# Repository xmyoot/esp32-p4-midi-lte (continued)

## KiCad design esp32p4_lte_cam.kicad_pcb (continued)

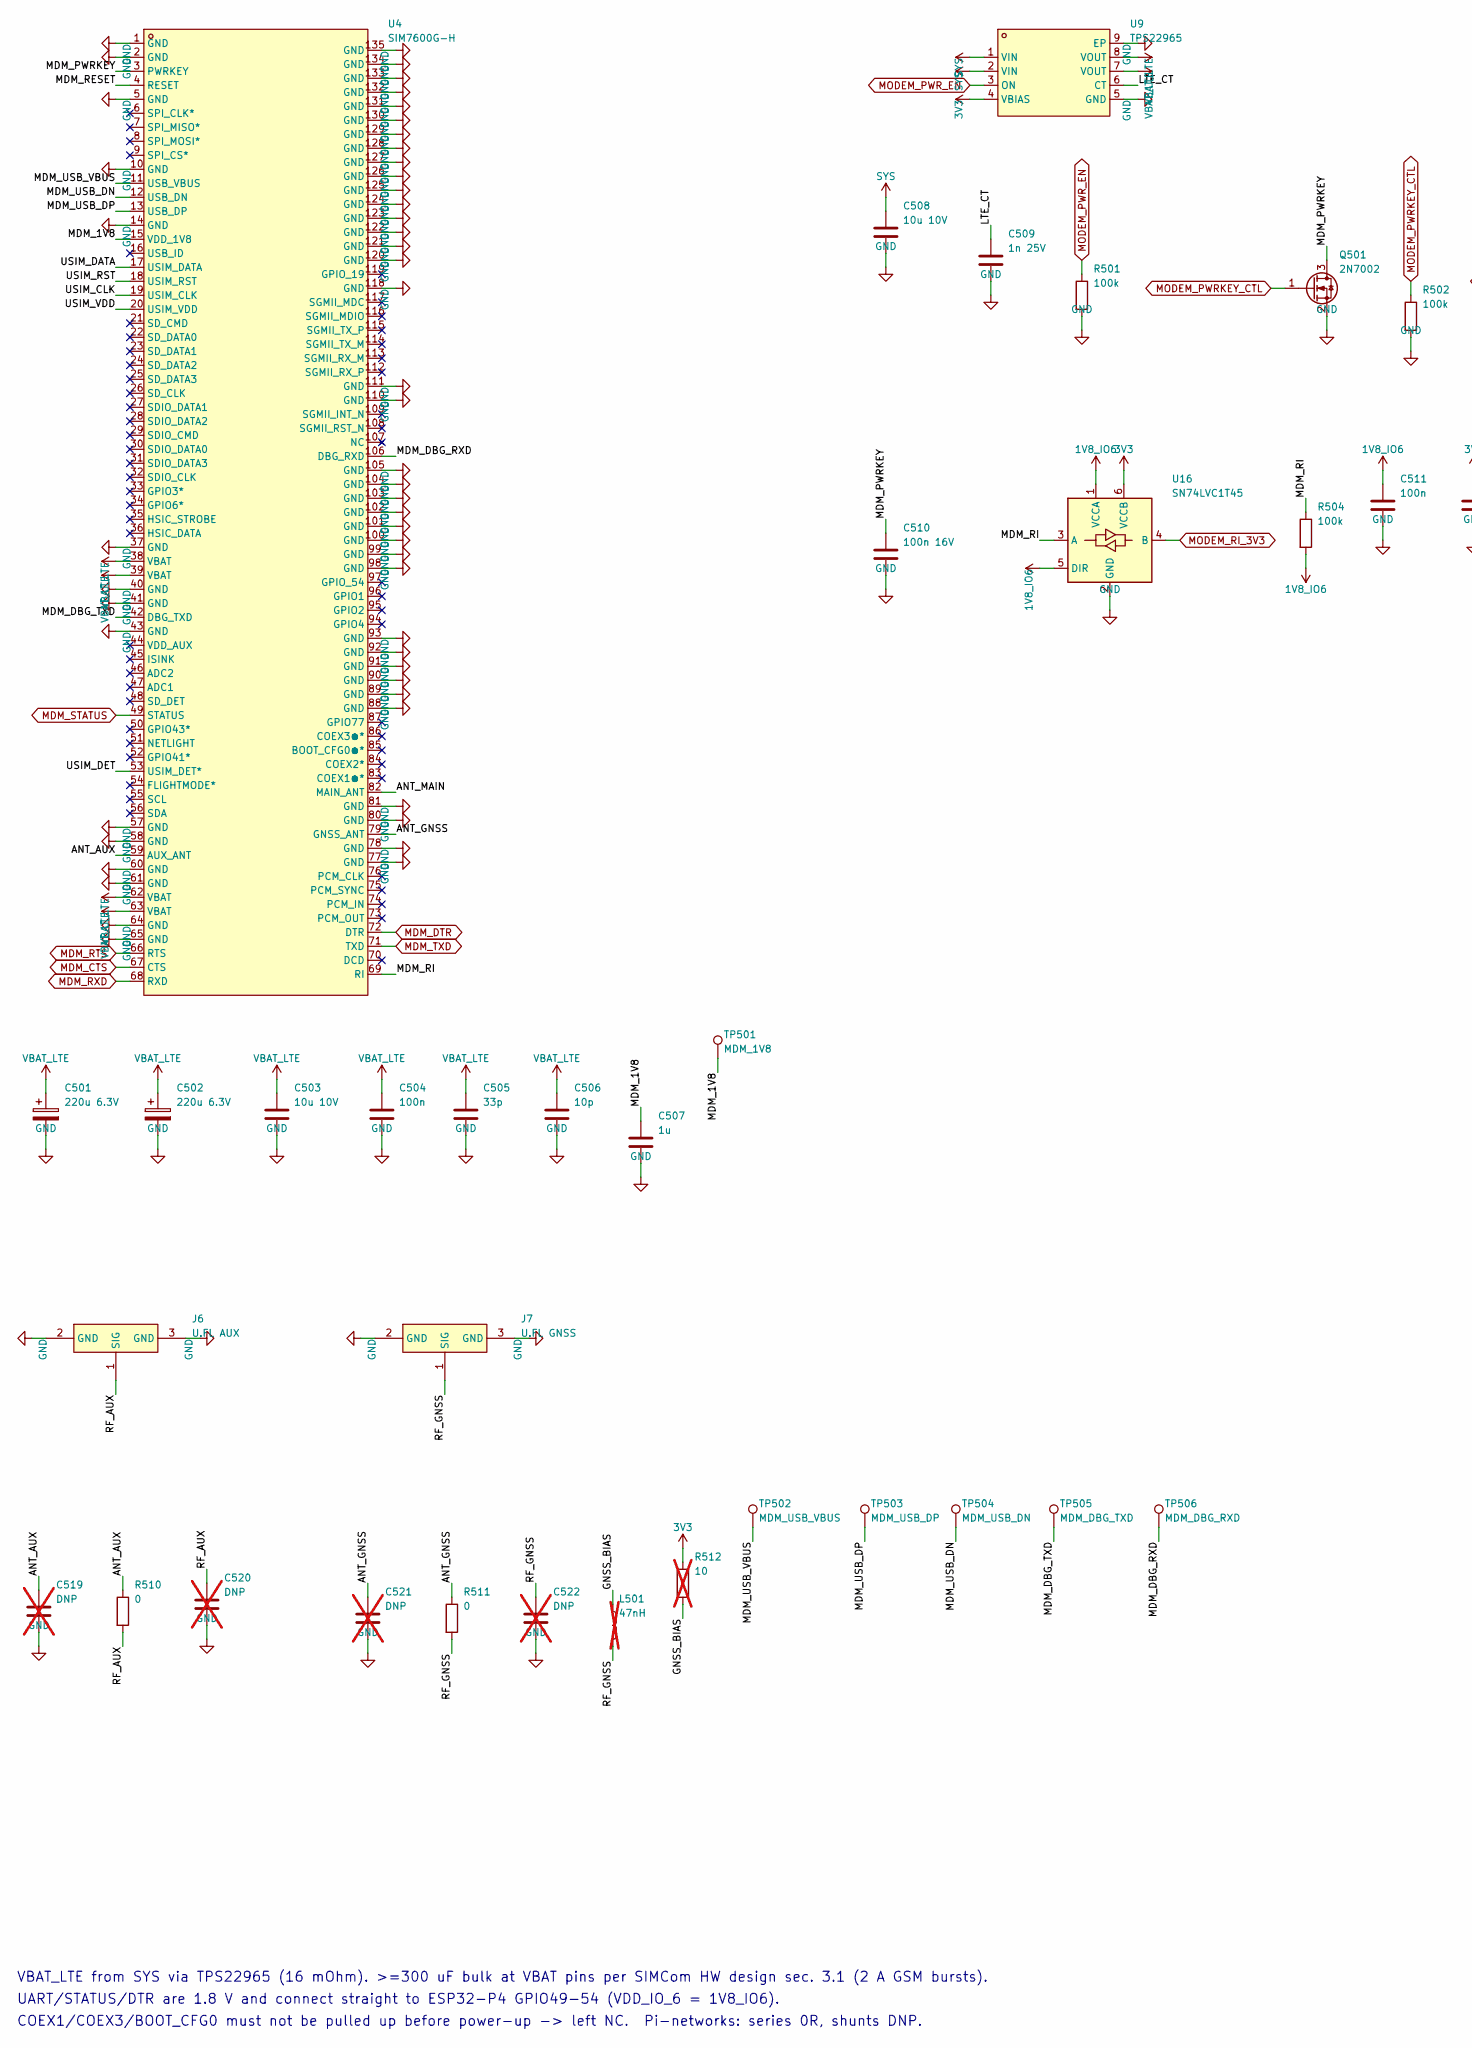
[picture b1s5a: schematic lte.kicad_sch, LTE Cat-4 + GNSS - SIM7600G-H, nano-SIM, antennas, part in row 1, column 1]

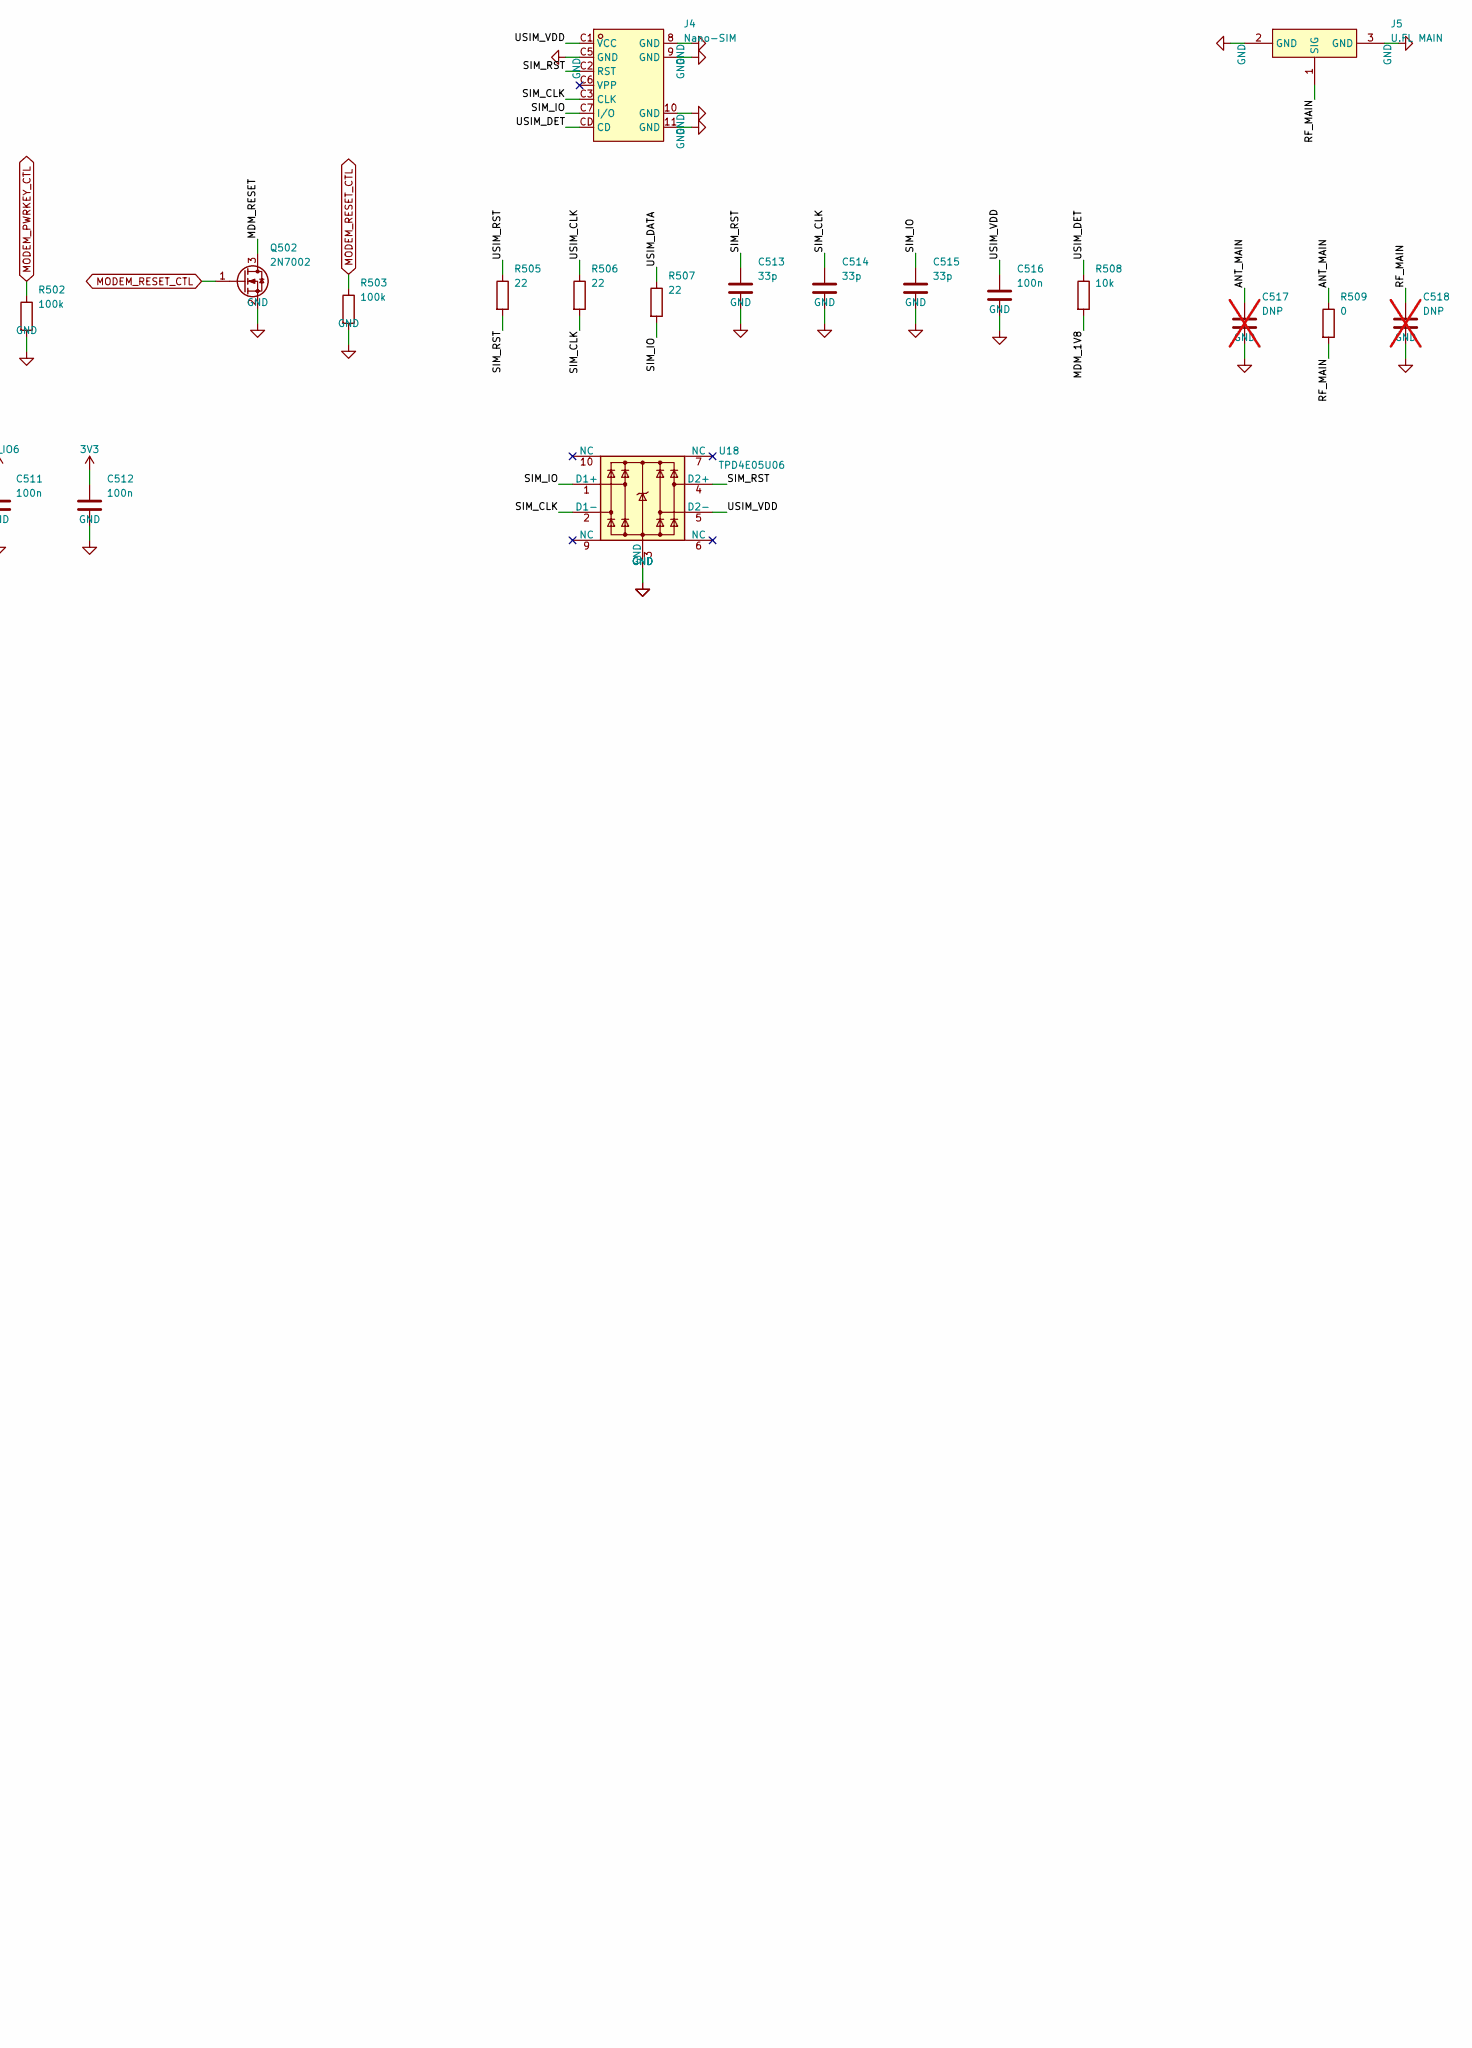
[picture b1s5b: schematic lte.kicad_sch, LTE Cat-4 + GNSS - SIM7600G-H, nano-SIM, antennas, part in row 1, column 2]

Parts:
C501, C502: 220u 6.3V; CP_EIA-3528-21_Kemet-B; MPN TLJB227M006R0500; LCSC C30242
C503: 10u 10V; C_0603_1608Metric; MPN CL10A106KP8NNNC; LCSC C19702
C504, C511, C512, C516: 100n; C_0402_1005Metric; MPN CL05B104KO5NNNC; LCSC C1525
C505, C513, C514, C515: 33p; C_0402_1005Metric; MPN 0402CG330J500NT; LCSC C1562
C506: 10p; C_0402_1005Metric; MPN CL05C100JB5NNNC; LCSC C32949
C507: 1u; C_0402_1005Metric; MPN CL05A105KA5NQNC; LCSC C52923
C508: 10u 10V; C_0805_2012Metric; MPN CL21A106KPFNNNE; LCSC C17024
C509: 1n 25V; C_0402_1005Metric; MPN CC0402KRX7R8BB102; LCSC C541372
C510: 100n 16V; C_0402_1005Metric; MPN CL05B104KO5NNNC; LCSC C1525
C517, C518, C519, C520, C521, C522: DNP; C_0402_1005Metric; not fitted
J4: Nano-SIM; SIM-SMD_NANO-SIM-7P-H1.37; MPN NANO SIM 7P H1.37; LCSC C7529384
J5: U.FL MAIN; RF-SMD_FRF05002-JSS103M; MPN U.FL-R-SMT-1(80); LCSC C88374
J6: U.FL AUX; RF-SMD_FRF05002-JSS103M; MPN U.FL-R-SMT-1(80); LCSC C88374
J7: U.FL GNSS; RF-SMD_FRF05002-JSS103M; MPN U.FL-R-SMT-1(80); LCSC C88374
L501: 47nH; L_0402_1005Metric; MPN SDCL1005C47NJTDF; LCSC C27151; not fitted
Q501, Q502: 2N7002; SOT-23; MPN 2N7002; LCSC C8545
R501, R502, R503, R504: 100k; R_0402_1005Metric; MPN 0402WGF1003TCE; LCSC C25741
R505, R506, R507: 22; R_0402_1005Metric; MPN 0402WGF220JTCE; LCSC C25092
R508: 10k; R_0402_1005Metric; MPN 0402WGF1002TCE; LCSC C25744
R509, R510, R511: 0; R_0402_1005Metric; MPN 0402WGF0000TCE; LCSC C17168
R512: 10; R_0402_1005Metric; MPN 0402WGF100JTCE; LCSC C25077; not fitted
TP501: MDM_1V8; TestPoint_Pad_D1.0mm
TP502: MDM_USB_VBUS; TestPoint_Pad_D1.0mm
TP503: MDM_USB_DP; TestPoint_Pad_D1.0mm
TP504: MDM_USB_DN; TestPoint_Pad_D1.0mm
TP505: MDM_DBG_TXD; TestPoint_Pad_D1.0mm
TP506: MDM_DBG_RXD; TestPoint_Pad_D1.0mm
U4: SIM7600G-H; COMM-SMD_135P-L30.0-W30.0_SIM7600G; MPN SIM7600G-H; LCSC C5355477
U9: TPS22965; UDFN-8_L2.0-W2.0-P0.50-TL-EP; MPN TPS22965DSGR; LCSC C122837
U16: SN74LVC1T45; SOT-23-6; MPN SN74LVC1T45DBVR; LCSC C7843
U18: TPD4E05U06; USON-10_2.5x1.0mm_P0.5mm; MPN TPD4E05U06DQAR; LCSC C138714

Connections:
1V8_IO6: C511.1, R504.2, U16.1 (VCCA), U16.5 (DIR); also elsewhere on the board
3V3: C512.1, R512.1, U9.4 (VBIAS), U16.6 (VCCB); also elsewhere on the board
/lte/ANT_AUX: C519.1, R510.1, U4.59 (AUX_ANT)
/lte/ANT_GNSS: C521.1, R511.1, U4.79 (GNSS_ANT)
/lte/ANT_MAIN: C517.1, R509.1, U4.82 (MAIN_ANT)
/lte/GNSS_BIAS: L501.1, R512.2
/lte/LTE_CT: C509.1, U9.6 (CT)
/lte/MDM_1V8: C507.1, R508.2, TP501.1, U4.15 (VDD_1V8)
/lte/MDM_DBG_RXD: TP506.1, U4.106 (DBG_RXD)
/lte/MDM_DBG_TXD: TP505.1, U4.42 (DBG_TXD)
/lte/MDM_PWRKEY: C510.1, Q501.3 (D), U4.3 (PWRKEY)
/lte/MDM_RESET: Q502.3 (D), U4.4 (RESET)
/lte/MDM_RI: R504.1, U4.69 (RI), U16.3 (A)
/lte/MDM_USB_DN: TP504.1, U4.12 (USB_DN)
/lte/MDM_USB_DP: TP503.1, U4.13 (USB_DP)
/lte/MDM_USB_VBUS: TP502.1, U4.11 (USB_VBUS)
/lte/RF_AUX: C520.1, J6.1 (SIG), R510.2
/lte/RF_GNSS: C522.1, J7.1 (SIG), L501.2, R511.2
/lte/RF_MAIN: C518.1, J5.1 (SIG), R509.2
/lte/SIM_CLK: C514.1, J4.C3 (CLK), R506.2, U18.2 (D1-)
/lte/SIM_IO: C515.1, J4.C7 (I/O), R507.2, U18.1 (D1+)
/lte/SIM_RST: C513.1, J4.C2 (RST), R505.2, U18.4 (D2+)
/lte/USIM_CLK: R506.1, U4.19 (USIM_CLK)
/lte/USIM_DATA: R507.1, U4.17 (USIM_DATA)
/lte/USIM_DET: J4.CD, R508.1, U4.53 (USIM_DET*)
/lte/USIM_RST: R505.1, U4.18 (USIM_RST)
/lte/USIM_VDD: C516.1, J4.C1 (VCC), U4.20 (USIM_VDD), U18.5 (D2-)
GND: C501.2, C502.2, C503.2, C504.2, C505.2, C506.2, C507.2, C508.2, C509.2, C510.2, C511.2, C512.2, C513.2, C514.2, C515.2, C516.2, C517.2, C518.2, C519.2, C520.2, C521.2, C522.2, J4.8 (GND), J4.9 (GND), J4.10 (GND), J4.11 (GND), J4.C5 (GND), J5.2 (GND), J5.3 (GND), J6.2 (GND), J6.3 (GND), J7.2 (GND), J7.3 (GND), Q501.2 (S), Q502.2 (S), R501.2, R502.2, R503.2, U4.1 (GND), U4.2 (GND), U4.5 (GND), U4.10 (GND), U4.14 (GND), U4.37 (GND), U4.40 (GND), U4.41 (GND), U4.43 (GND), U4.57 (GND), U4.58 (GND), U4.60 (GND), U4.61 (GND), U4.64 (GND), U4.65 (GND), U4.77 (GND), U4.78 (GND), U4.80 (GND), U4.81 (GND), U4.88 (GND), U4.89 (GND), U4.90 (GND), U4.91 (GND), U4.92 (GND), U4.93 (GND), U4.98 (GND), U4.99 (GND), U4.100 (GND), U4.101 (GND), U4.102 (GND), U4.103 (GND), U4.104 (GND), U4.105 (GND), U4.110 (GND), U4.111 (GND), U4.118 (GND), U4.120 (GND), U4.121 (GND), U4.122 (GND), U4.123 (GND), U4.124 (GND), U4.125 (GND), U4.126 (GND), U4.127 (GND), U4.128 (GND), U4.129 (GND), U4.130 (GND), U4.131 (GND), U4.132 (GND), U4.133 (GND), U4.134 (GND), U4.135 (GND), U9.5 (GND), U9.9 (EP), U16.2 (GND), U18.3 (GND), U18.8 (GND); also elsewhere on the board
MDM_CTS: U4.67 (CTS); also elsewhere on the board
MDM_DTR: U4.72 (DTR); also elsewhere on the board
MDM_RTS: U4.66 (RTS); also elsewhere on the board
MDM_RXD: U4.68 (RXD); also elsewhere on the board
MDM_STATUS: U4.49 (STATUS); also elsewhere on the board
MDM_TXD: U4.71 (TXD); also elsewhere on the board
MODEM_PWRKEY_CTL: Q501.1 (G), R502.1; also elsewhere on the board
MODEM_PWR_EN: R501.1, U9.3 (ON); also elsewhere on the board
MODEM_RESET_CTL: Q502.1 (G), R503.1; also elsewhere on the board
MODEM_RI_3V3: U16.4 (B); also elsewhere on the board
SYS: C508.1, U9.1 (VIN), U9.2 (VIN); also elsewhere on the board
VBAT_LTE: C501.1, C502.1, C503.1, C504.1, C505.1, C506.1, U4.38 (VBAT), U4.39 (VBAT), U4.62 (VBAT), U4.63 (VBAT), U9.7 (VOUT), U9.8 (VOUT)

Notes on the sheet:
VBAT_LTE from SYS via TPS22965 (16 mOhm). >=300 uF bulk at VBAT pins per SIMCom HW design sec. 3.1 (2 A GSM bursts).
UART/STATUS/DTR are 1.8 V and connect straight to ESP32-P4 GPIO49-54 (VDD_IO_6 = 1V8_IO6).
COEX1/COEX3/BOOT_CFG0 must not be pulled up before power-up -> left NC. Pi-networks: series 0R, shunts DNP.

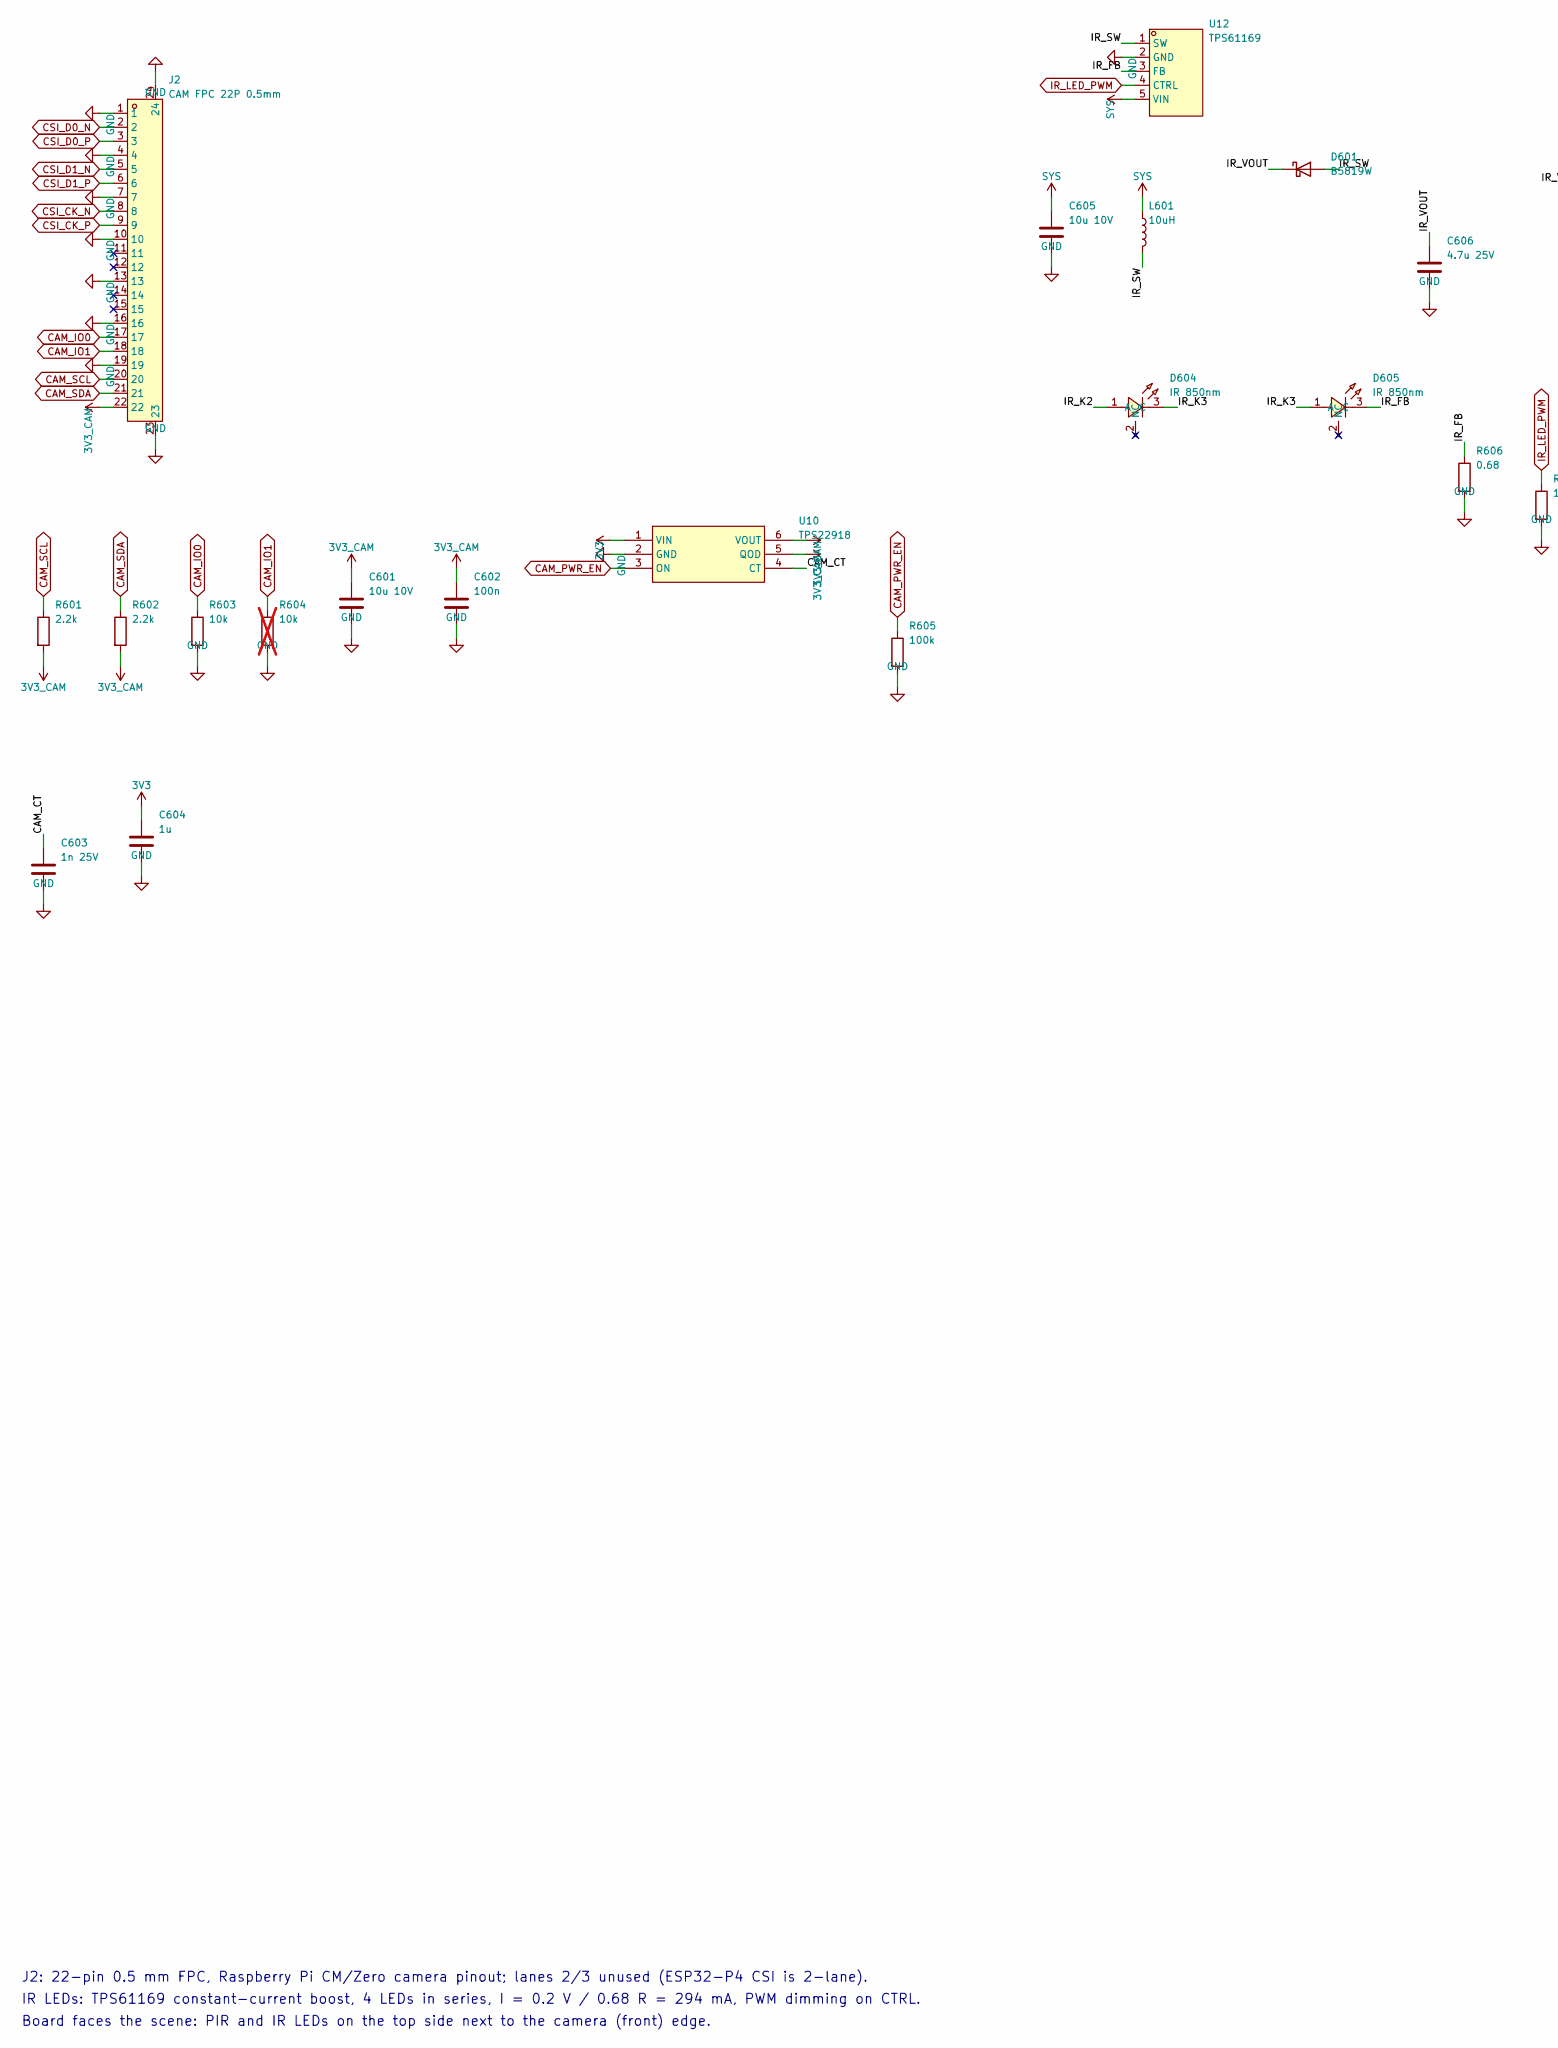
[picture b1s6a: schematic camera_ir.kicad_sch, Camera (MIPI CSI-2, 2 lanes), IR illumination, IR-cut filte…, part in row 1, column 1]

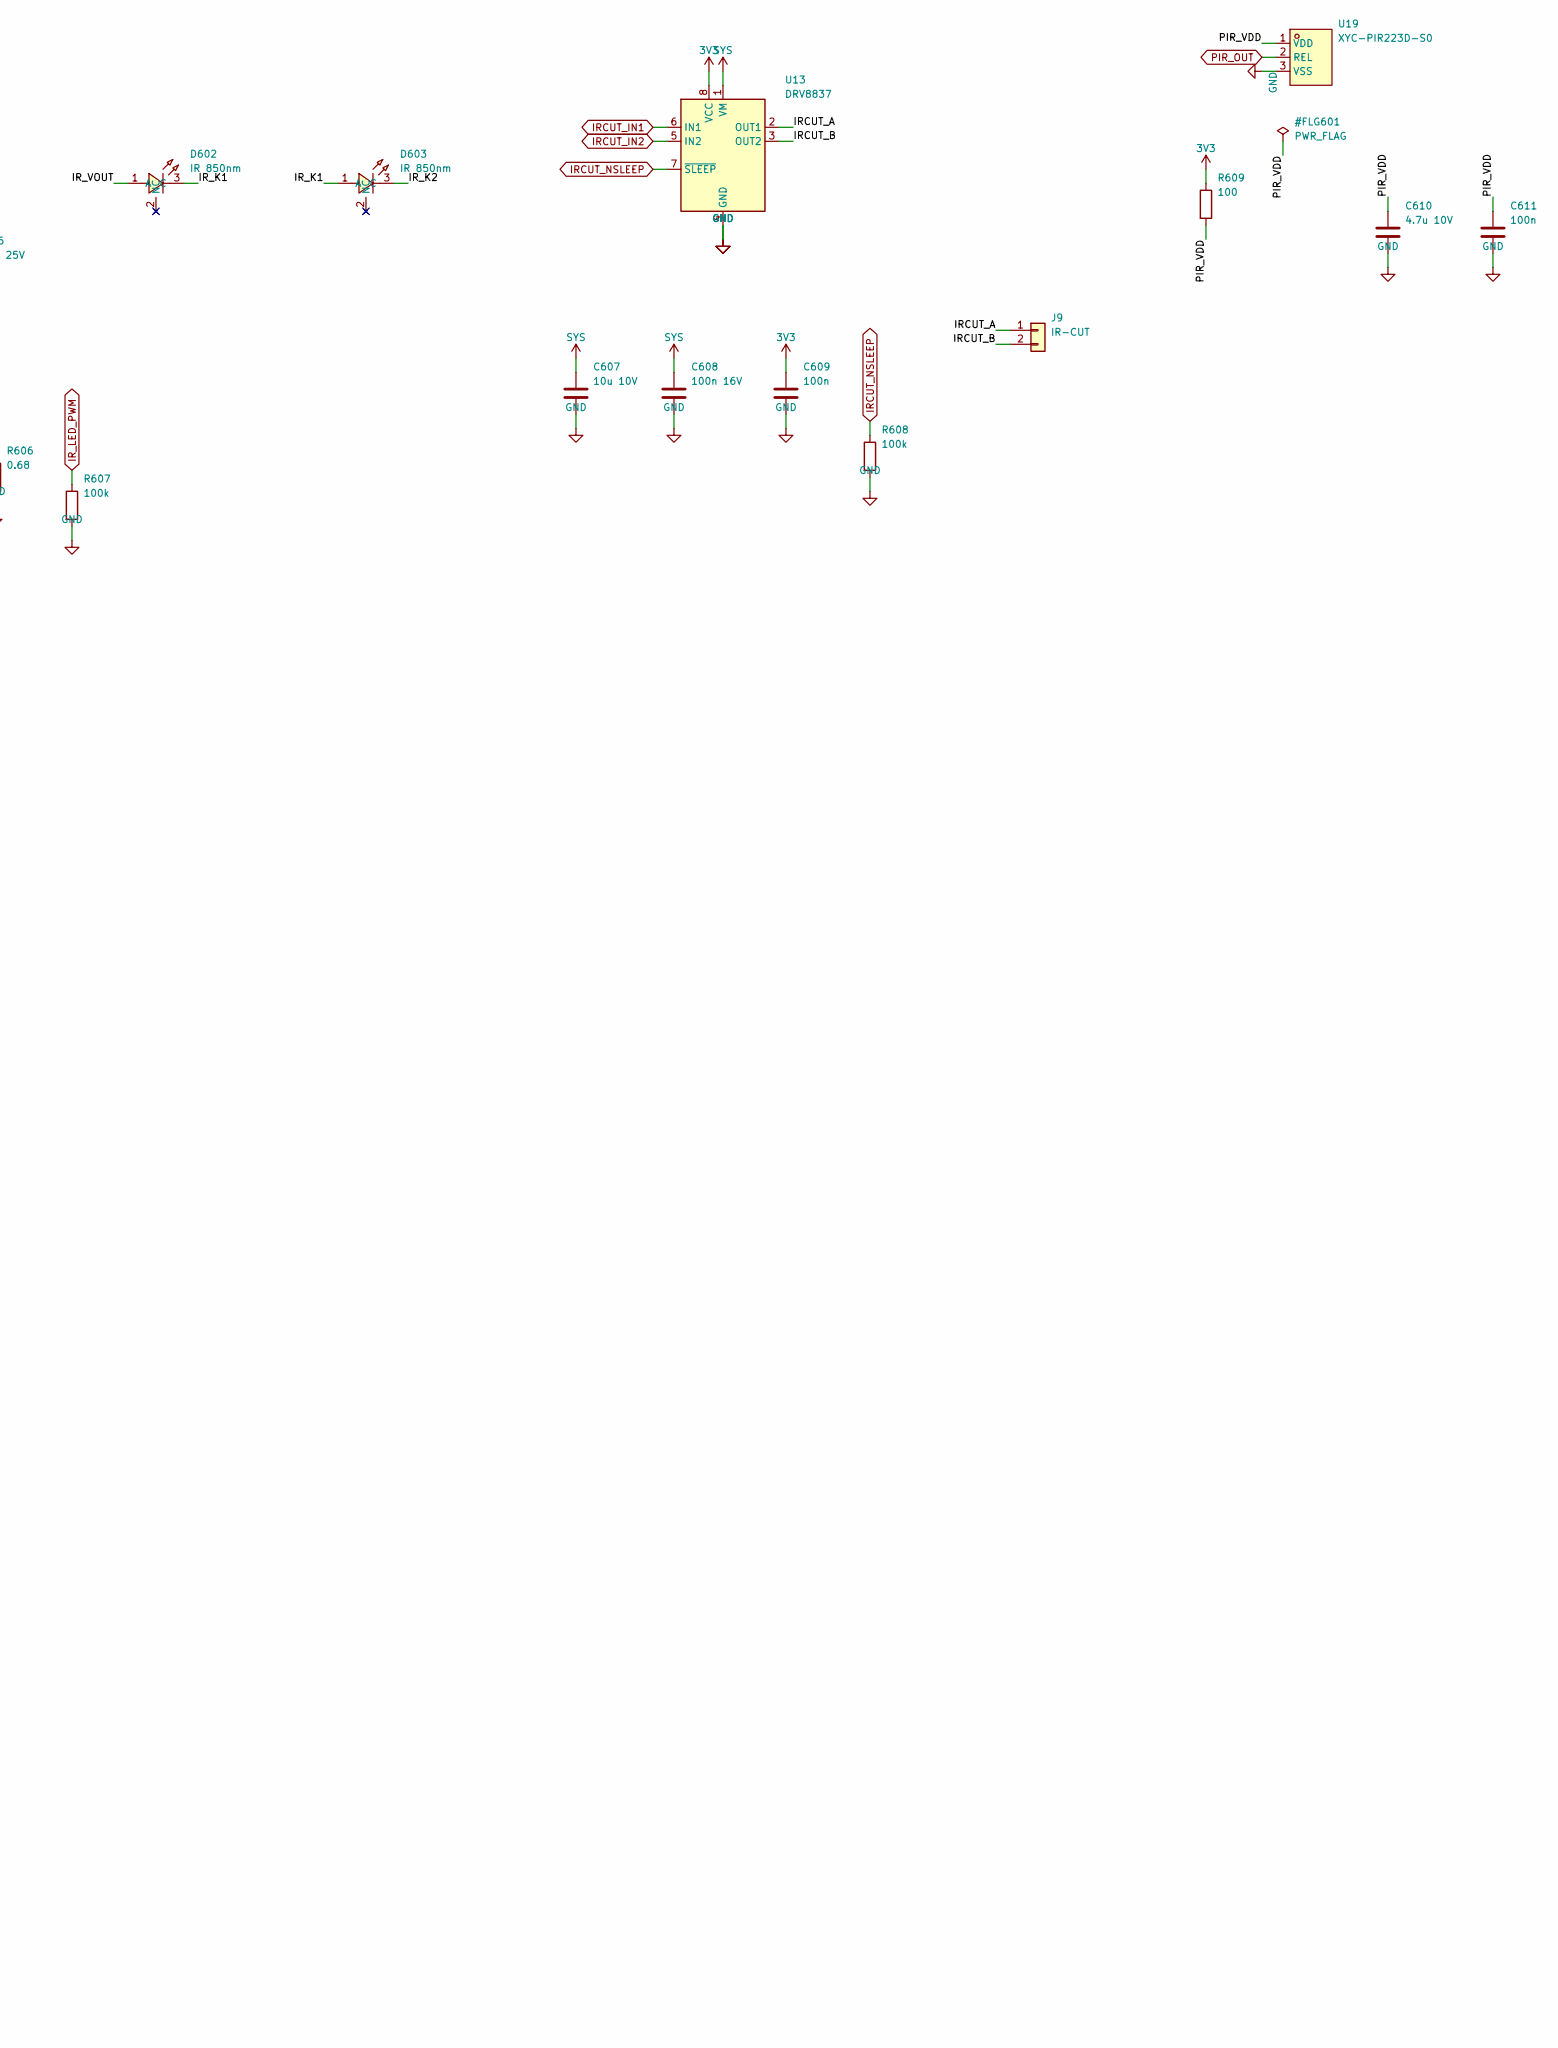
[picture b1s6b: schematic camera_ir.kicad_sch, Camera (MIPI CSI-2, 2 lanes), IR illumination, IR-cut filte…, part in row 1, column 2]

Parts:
C601: 10u 10V; C_0603_1608Metric; MPN CL10A106KP8NNNC; LCSC C19702
C602, C609, C611: 100n; C_0402_1005Metric; MPN CL05B104KO5NNNC; LCSC C1525
C603: 1n 25V; C_0402_1005Metric; MPN CC0402KRX7R8BB102; LCSC C541372
C604: 1u; C_0402_1005Metric; MPN CL05A105KA5NQNC; LCSC C52923
C605, C607: 10u 10V; C_0805_2012Metric; MPN CL21A106KPFNNNE; LCSC C17024
C606: 4.7u 25V; C_0805_2012Metric; MPN CL21A475KAQNNNE; LCSC C1779
C608: 100n 16V; C_0402_1005Metric; MPN CL05B104KO5NNNC; LCSC C1525
C610: 4.7u 10V; C_0603_1608Metric; MPN CL10A475KP8NNNC; LCSC C1705
D601: B5819W; D_SOD-123; MPN B5819W SL; LCSC C8598
D602, D603, D604, D605: IR 850nm; LED-SMD_3P-L3.8-W3.8_M3838E1IRS1G09; MPN M3838E1IRS1G09-850NM; LCSC C2833567
J2: CAM FPC 22P 0.5mm; CONN-SMD_05B20L22P; MPN 05B20L22P; LCSC C22459552
J9: IR-CUT; JST_SH_SM02B-SRSS-TB_1x02-1MP_P1.00mm_Horizontal; MPN SM02B-SRSS-TB(LF)(SN); LCSC C160402
L601: 10uH; IND-SMD_L4.0-W4.0; MPN SWPA4030S100MT; LCSC C38117
R601, R602: 2.2k; R_0402_1005Metric; MPN 0402WGF2201TCE; LCSC C25879
R603: 10k; R_0402_1005Metric; MPN 0402WGF1002TCE; LCSC C25744
R604: 10k; R_0402_1005Metric; MPN 0402WGF1002TCE; LCSC C25744; not fitted
R605, R607, R608: 100k; R_0402_1005Metric; MPN 0402WGF1003TCE; LCSC C25741
R606: 0.68; R_0805_2012Metric; MPN 0805W8F680LT5E; LCSC C47389
R609: 100; R_0402_1005Metric; MPN 0402WGF1000TCE; LCSC C25076
U10: TPS22918; SOT-23-6_L2.9-W1.6-P0.95-LS2.8-BR; MPN TPS22918DBVR; LCSC C131941
U12: TPS61169; SC-70-5_L2.1-W1.3-P0.65-LS2.1-BR; MPN TPS61169DCKR; LCSC C71045
U13: DRV8837; Texas_DSG0008A_WSON-8-1EP_2x2mm_P0.5mm_EP0.9x1.6mm; MPN DRV8837DSGR; LCSC C39159
U19: XYC-PIR223D-S0; TO-5-3_L8.2-W8.2; MPN XYC-PIR223D-S0; LCSC C2887901

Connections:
3V3: C604.1, C609.1, R609.1, U10.1 (VIN), U13.8 (VCC); also elsewhere on the board
3V3_CAM: C601.1, C602.1, J2.22, R601.2, R602.2, U10.5 (QOD), U10.6 (VOUT)
/camera_ir/CAM_CT: C603.1, U10.4 (CT)
/camera_ir/IRCUT_A: J9.1, U13.2 (OUT1)
/camera_ir/IRCUT_B: J9.2, U13.3 (OUT2)
/camera_ir/IR_FB: D605.3 (C), R606.1, U12.3 (FB)
/camera_ir/IR_K1: D602.3 (C), D603.1 (A)
/camera_ir/IR_K2: D603.3 (C), D604.1 (A)
/camera_ir/IR_K3: D604.3 (C), D605.1 (A)
/camera_ir/IR_SW: D601.2 (A), L601.2, U12.1 (SW)
/camera_ir/IR_VOUT: C606.1, D601.1 (K), D602.1 (A)
/camera_ir/PIR_VDD: C610.1, C611.1, R609.2, U19.1 (VDD)
CAM_IO0: J2.17, R603.1; also elsewhere on the board
CAM_IO1: J2.18, R604.1; also elsewhere on the board
CAM_PWR_EN: R605.1, U10.3 (ON); also elsewhere on the board
CAM_SCL: J2.20, R601.1; also elsewhere on the board
CAM_SDA: J2.21, R602.1; also elsewhere on the board
CSI_CK_N: J2.8; also elsewhere on the board
CSI_CK_P: J2.9; also elsewhere on the board
CSI_D0_N: J2.2; also elsewhere on the board
CSI_D0_P: J2.3; also elsewhere on the board
CSI_D1_N: J2.5; also elsewhere on the board
CSI_D1_P: J2.6; also elsewhere on the board
GND: C601.2, C602.2, C603.2, C604.2, C605.2, C606.2, C607.2, C608.2, C609.2, C610.2, C611.2, J2.1, J2.4, J2.7, J2.10, J2.13, J2.16, J2.19, J2.23, J2.24, R603.2, R604.2, R605.2, R606.2, R607.2, R608.2, U10.2 (GND), U12.2 (GND), U13.4 (GND), U13.9 (GND), U19.3 (VSS); also elsewhere on the board
IRCUT_IN1: U13.6 (IN1); also elsewhere on the board
IRCUT_IN2: U13.5 (IN2); also elsewhere on the board
IRCUT_NSLEEP: R608.1, U13.7 (~SLEEP); also elsewhere on the board
IR_LED_PWM: R607.1, U12.4 (CTRL); also elsewhere on the board
PIR_OUT: U19.2 (REL); also elsewhere on the board
SYS: C605.1, C607.1, C608.1, L601.1, U12.5 (VIN), U13.1 (VM); also elsewhere on the board

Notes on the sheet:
J2: 22-pin 0.5 mm FPC, Raspberry Pi CM/Zero camera pinout; lanes 2/3 unused (ESP32-P4 CSI is 2-lane).
IR LEDs: TPS61169 constant-current boost, 4 LEDs in series, I = 0.2 V / 0.68 R = 294 mA, PWM dimming on CTRL.
Board faces the scene: PIR and IR LEDs on the top side next to the camera (front) edge.

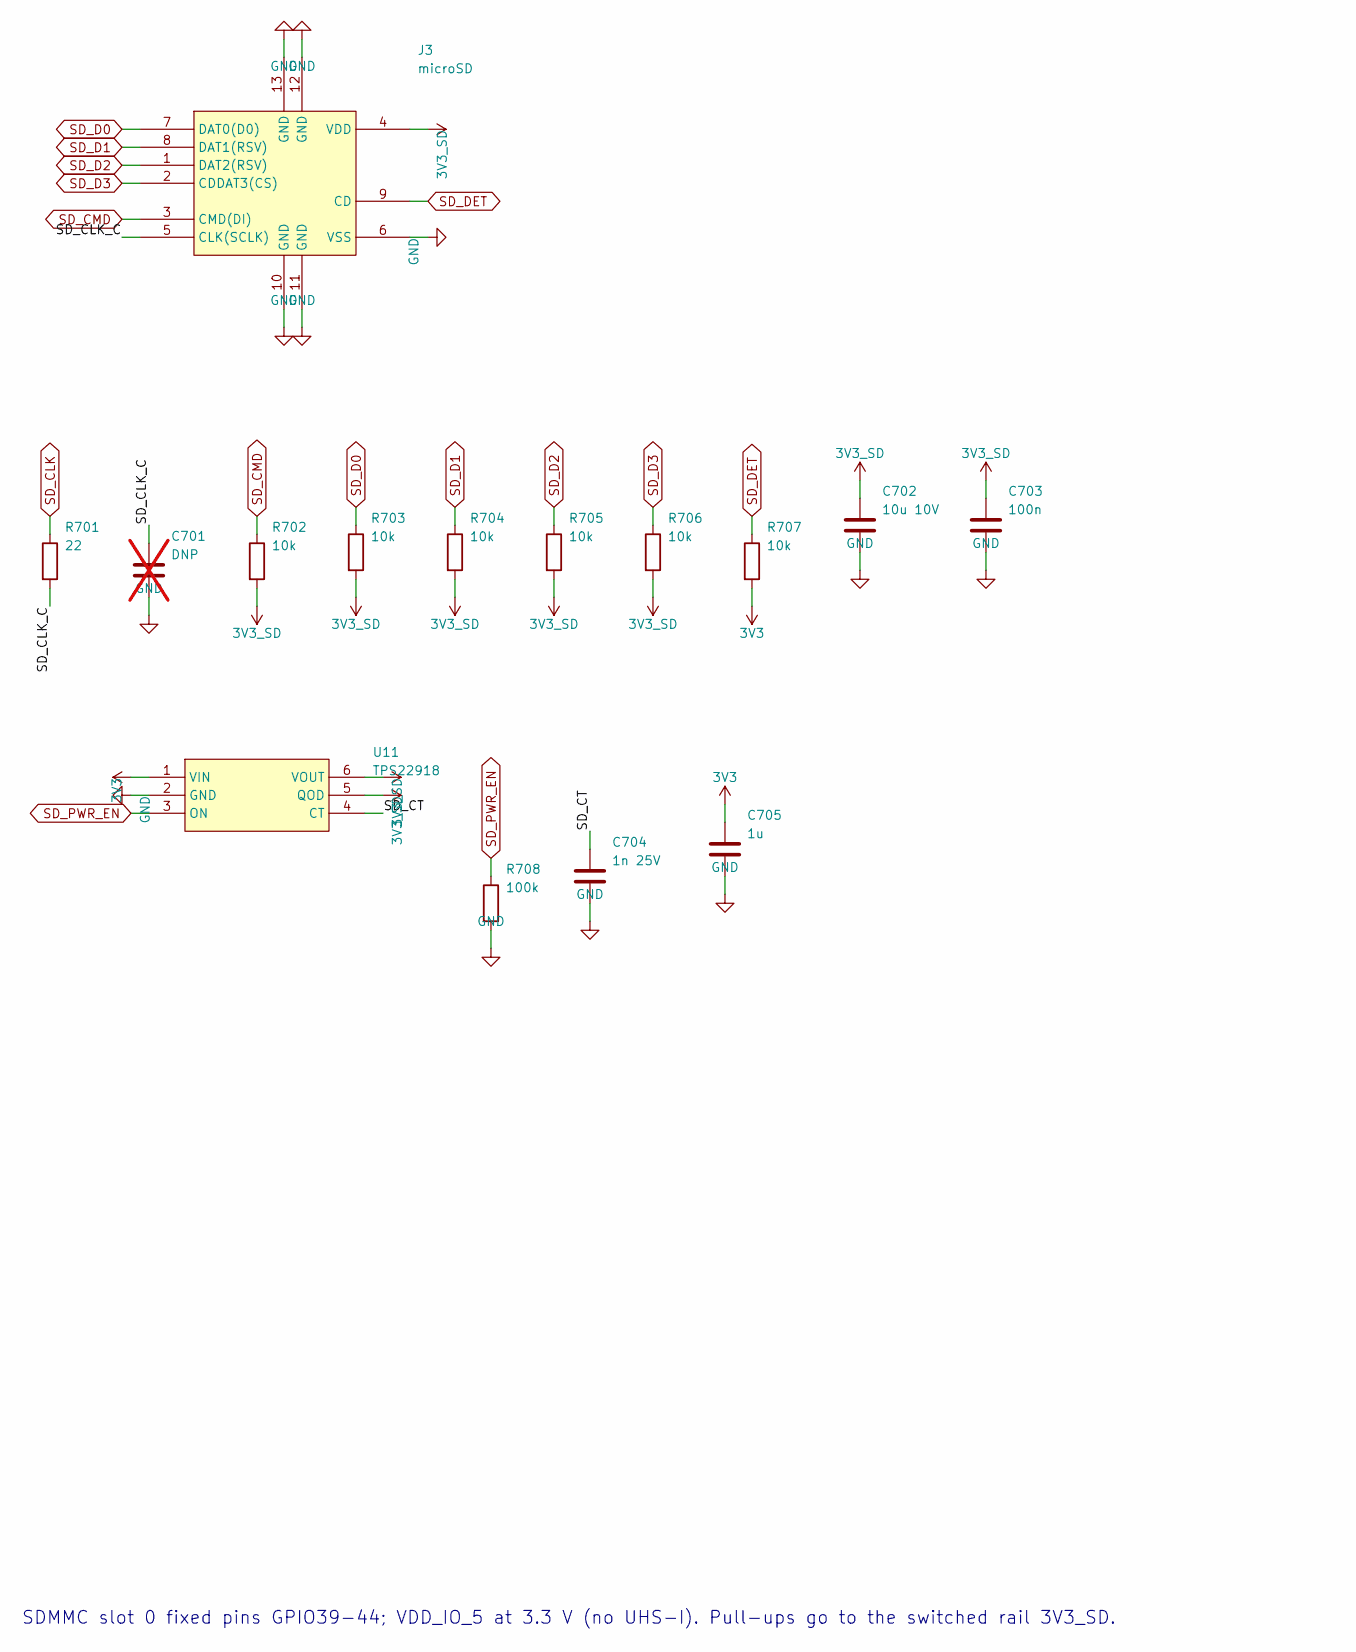
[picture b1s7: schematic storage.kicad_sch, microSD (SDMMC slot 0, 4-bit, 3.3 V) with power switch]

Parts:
C701: DNP; C_0402_1005Metric; not fitted
C702: 10u 10V; C_0603_1608Metric; MPN CL10A106KP8NNNC; LCSC C19702
C703: 100n; C_0402_1005Metric; MPN CL05B104KO5NNNC; LCSC C1525
C704: 1n 25V; C_0402_1005Metric; MPN CC0402KRX7R8BB102; LCSC C541372
C705: 1u; C_0402_1005Metric; MPN CL05A105KA5NQNC; LCSC C52923
J3: microSD; TF-SMD_TF-01A; MPN TF-01A; LCSC C91145
R701: 22; R_0402_1005Metric; MPN 0402WGF220JTCE; LCSC C25092
R702, R703, R704, R705, R706, R707: 10k; R_0402_1005Metric; MPN 0402WGF1002TCE; LCSC C25744
R708: 100k; R_0402_1005Metric; MPN 0402WGF1003TCE; LCSC C25741
U11: TPS22918; SOT-23-6_L2.9-W1.6-P0.95-LS2.8-BR; MPN TPS22918DBVR; LCSC C131941

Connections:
3V3: C705.1, R707.2, U11.1 (VIN); also elsewhere on the board
3V3_SD: C702.1, C703.1, J3.4 (VDD), R702.2, R703.2, R704.2, R705.2, R706.2, U11.5 (QOD), U11.6 (VOUT)
/storage/SD_CLK_C: C701.1, J3.5 (CLK(SCLK)), R701.2
/storage/SD_CT: C704.1, U11.4 (CT)
GND: C701.2, C702.2, C703.2, C704.2, C705.2, J3.6 (VSS), J3.10 (GND), J3.11 (GND), J3.12 (GND), J3.13 (GND), R708.2, U11.2 (GND); also elsewhere on the board
SD_CLK: R701.1; also elsewhere on the board
SD_CMD: J3.3 (CMD(DI)), R702.1; also elsewhere on the board
SD_D0: J3.7 (DAT0(D0)), R703.1; also elsewhere on the board
SD_D1: J3.8 (DAT1(RSV)), R704.1; also elsewhere on the board
SD_D2: J3.1 (DAT2(RSV)), R705.1; also elsewhere on the board
SD_D3: J3.2 (CDDAT3(CS)), R706.1; also elsewhere on the board
SD_DET: J3.9 (CD), R707.1; also elsewhere on the board
SD_PWR_EN: R708.1, U11.3 (ON); also elsewhere on the board

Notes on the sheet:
SDMMC slot 0 fixed pins GPIO39-44; VDD_IO_5 at 3.3 V (no UHS-I). Pull-ups go to the switched rail 3V3_SD.
